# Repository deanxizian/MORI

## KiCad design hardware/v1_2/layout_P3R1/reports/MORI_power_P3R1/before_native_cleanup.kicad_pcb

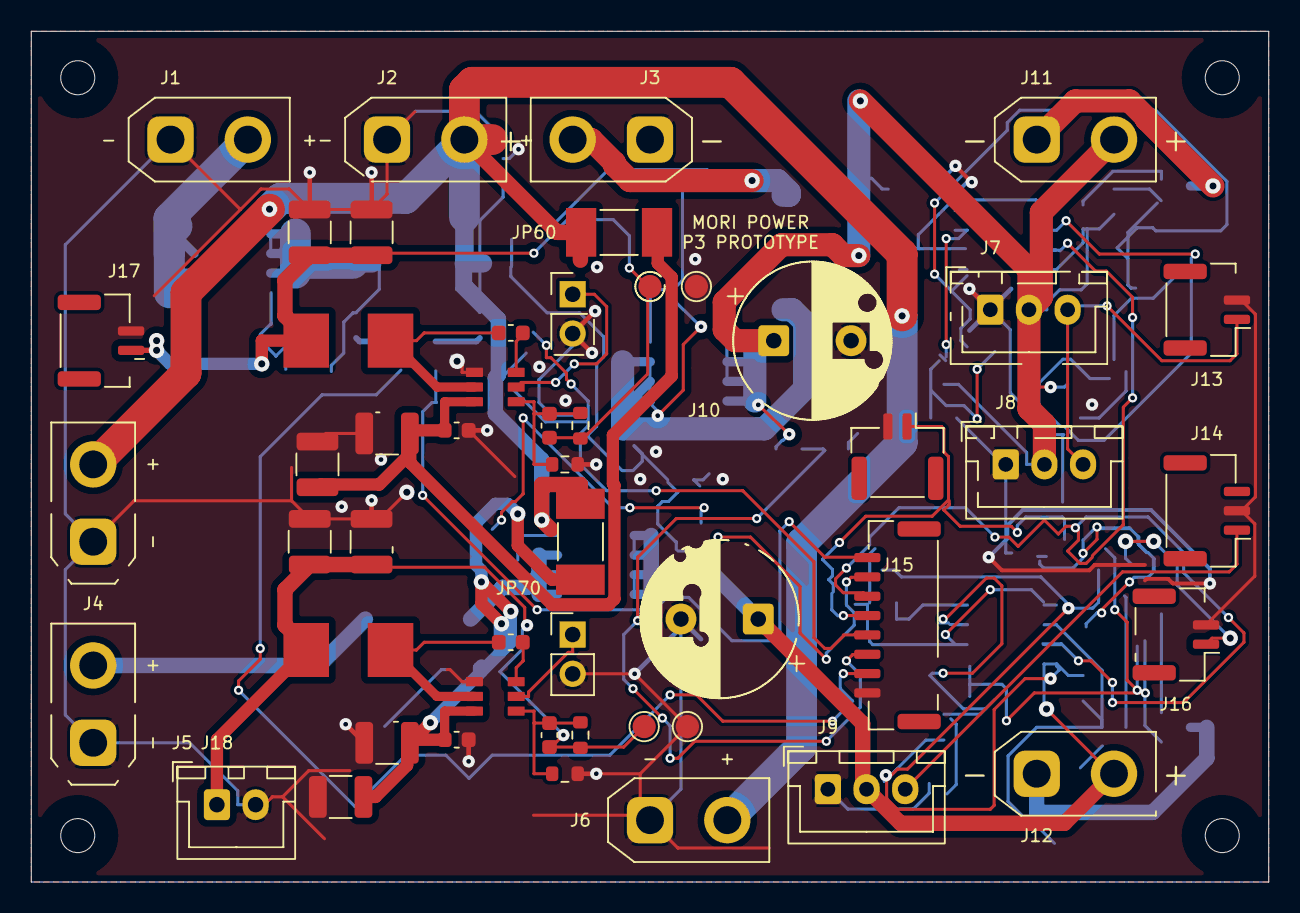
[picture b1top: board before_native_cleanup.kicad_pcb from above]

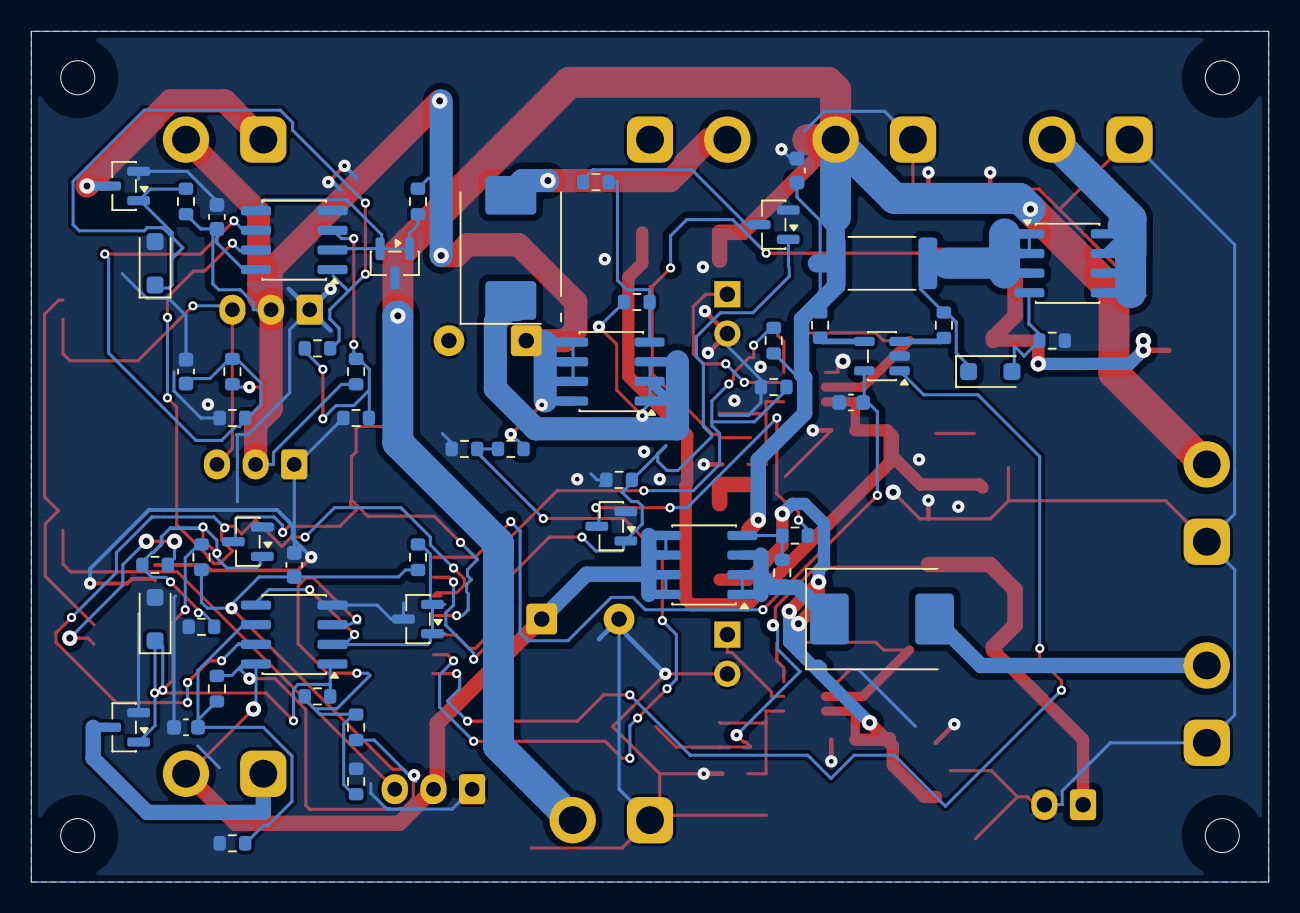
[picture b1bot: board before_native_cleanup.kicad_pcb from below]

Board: 2 copper layers, 80.0 x 55.0 mm, 107 parts (53 on the bottom side), 50 nets.

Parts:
C1, C20, C40: 100n; C_0603_1608Metric
C2: 1u 25V; C_0603_1608Metric__P3_C2
C10: Panasonic EEU-FR1C102 1000uF 16V; CP_Radial_D10.0mm_P5.00mm__P2_C10__P3_C10
C21, C41: 10n; C_0603_1608Metric
C30: Panasonic EEU-FR1C102 1000uF 16V; CP_Radial_D10.0mm_P5.00mm__P3_C30
C60: 22u / 25V / X7R; C_1210_3225Metric__P3_C60
C61, C62, C71, C72: 100n / 50V / X7R; C_0603_1608Metric
C63, C64, C66, C73, C76: 22u / 25V / X7R; C_1210_3225Metric
C65, C75: 75p / 50V / C0G; C_0603_1608Metric
C70: 22u / 25V / X7R; C_1210_3225Metric__P3_C70
C74: 22u / 25V / X7R; C_1210_3225Metric__P3_C74
D1, D20, D40: BZT52H-C10,115; D_SOD-123F
D10: B540C-13-F; D_SMC__P3_D10
D30: B540C-13-F; D_SMC
F60: 1A / 125V / very fast; Fuse_Littelfuse-NANO2-451_453
F70: 2A / 125V / very fast; Fuse_Littelfuse-NANO2-451_453
H1, H2, H3, H4: M2 mounting / POSITION TBD; MountingHole_2.2mm_M2
J1: PACK AFTER 6.3A FUSE / MASTER; AMASS_XT30UPB-M_1x02_P5.0mm_Vertical__P3_J1
J2: WHEEL BUCK VIN; AMASS_XT30UPB-M_1x02_P5.0mm_Vertical__P3_J2
J3: WHEEL BUCK 9V RETURN; AMASS_XT30UPB-M_1x02_P5.0mm_Vertical
J4: HEAD BUCK VIN; AMASS_XT30UPB-M_1x02_P5.0mm_Vertical__P2_J4__P3_J4
J5: HEAD BUCK 6V RETURN; AMASS_XT30UPB-M_1x02_P5.0mm_Vertical__P2_J5__P3_J5
J6: RAW BAT SERVICE / DNP; AMASS_XT30UPB-M_1x02_P5.0mm_Vertical__P3_J6
J7: S288 L; JST_XH_B3B-XH-A_1x03_P2.50mm_Vertical__P2_J7__P3_J7
J8: S288 R; JST_XH_B3B-XH-A_1x03_P2.50mm_Vertical__P2_J8
J9: SCS0009 CHAIN; JST_XH_B3B-XH-A_1x03_P2.50mm_Vertical
J10: MOTION CONTROL; JST_GH_BM08B-GHS-TBT_1x08-1MP_P1.25mm_Vertical__P2_J10__P3_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
J11: WHEEL DUMP 5R6 EXTERNAL; AMASS_XT30UPB-M_1x02_P5.0mm_Vertical
J12: HEAD DUMP 10R EXTERNAL; AMASS_XT30UPB-M_1x02_P5.0mm_Vertical__P2_J12
J13: S288 DATA; JST_GH_BM02B-GHS-TBT_1x02-1MP_P1.25mm_Vertical__P2_J13
J14: HEAD DATA; JST_GH_BM03B-GHS-TBT_1x03-1MP_P1.25mm_Vertical
J15: CHARGE INTERLOCK; JST_GH_BM02B-GHS-TBT_1x02-1MP_P1.25mm_Vertical
J16: CHARGER RAW VBUS SENSE; JST_GH_BM02B-GHS-TBT_1x02-1MP_P1.25mm_Vertical__P2_J16
J17: MOTION 5V OUT / 1+ 2GND; JST_GH_BM02B-GHS-TBT_1x02-1MP_P1.25mm_Vertical__P3_J17
J18: CAM 5V OUT / 1+ 2GND; JST_XH_B2B-XH-A_1x02_P2.50mm_Vertical
JP60: SERVICE OFF / OPEN=ON; PinHeader_1x02_P2.54mm_Vertical__P3_JP60
JP70: SERVICE OFF / OPEN=ON; PinHeader_1x02_P2.54mm_Vertical
L60, L70: 10uH / SRP7050TA-100M; Bourns_SRP7050TA_8p4_span_2p5_gap
Q1, Q10, Q30: AO4407A; SOIC-8_3.9x4.9mm_P1.27mm
Q11, Q20, Q31, Q40: AO3400A; SOT-23
Q50: MMBT3904LT1G; SOT-23
R1, R10, R30, R54: 10k; R_0603_1608Metric
R2: WSL2512R0100FEA 10mR 1% 1W; R_2512_6332Metric
R3, R4: 0; R_0603_1608Metric
R11, R31: 100; R_0603_1608Metric
R20, R24, R40, R44: 2.2k; R_0603_1608Metric
R21: 33.2k 0.1%; R_0603_1608Metric
R22, R26, R42, R46: 10k 0.1%; R_0603_1608Metric
R23, R43: 1M 0.1%; R_0603_1608Metric
R25: 37.4k 0.1%; R_0603_1608Metric
R41: 16.5k 0.1%; R_0603_1608Metric
R45: 18.7k 0.1%; R_0603_1608Metric
R50, R52: 100k 0.1%; R_0603_1608Metric
R51, R53: 27k 0.1%; R_0603_1608Metric
R55: 47k; R_0603_1608Metric
R56: 100k; R_0603_1608Metric
R60, R70: 100k / 0.1%; R_0603_1608Metric
R61: 13.3k / 0.1%; R_0603_1608Metric
R71: 13.3k / 0.1%; R_0603_1608Metric__P3_R71
TP60: +5V_MOTION; TestPoint_Pad_D1.5mm__P3_TP60
TP61, TP71: GND; TestPoint_Pad_D1.5mm
TP70: +5V_CAM; TestPoint_Pad_D1.5mm
U1: INA180A1IDBVR; SOT-23-5
U20, U40: LM393BDR; SOIC-8_3.9x4.9mm_P1.27mm
U21, U41: TL431BIDBZR; SOT-23
U60, U70: TPS54302DDCR; TI_DDC0006A_TPS54302

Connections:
/+3V3: C1.1, J10.1, U1.5
/+5V_CAM: C73.1, C74.1, C75.1, J18.1, L70.2, R70.1, TP70.1
/+5V_MOTION: C63.1, C64.1, C65.1, J17.1, L60.2, R60.1, TP60.1
/ARM_Q: J10.2, Q11.1, Q31.1, R54.1
/BAT_ADC: J10.5, R50.2, R51.1
/BAT_IN: J1.2, Q1.5, Q1.6, Q1.7, Q1.8
/BAT_MON: C2.1, F60.1, F70.1, J2.2, J4.2, J6.2, R2.2, R4.1, R50.1
/BAT_REV: D1.1, Q1.1, Q1.2, Q1.3, R2.1, R3.1
/C5_BOOT: C72.1, U70.6
/C5_EN: JP70.1, U70.5
/C5_FB: C75.2, R70.2, R71.1, U70.4
/C5_SW: C72.2, L70.1, U70.2
/C5_VIN: C70.1, C71.1, C76.1, F70.2, U70.3
/CHG_BASE: Q50.1, R55.2, R56.1
/CHG_N: J10.4, J15.1, Q50.3
/CURRENT_ADC: J10.7, U1.1
/FAULT_N: J10.3, U20.7, U40.7
/GND: C1.2, C2.2, C10.2, C20.2, C21.2, C30.2, C40.2, C41.2, C60.2, C61.2, C63.2, C64.2, C66.2, C70.2, C71.2, C73.2, C74.2, C76.2, D20.2, D40.2, J1.1, J2.1, J3.1, J4.1, J5.1, J6.1, J7.1, J8.1, J9.1, J10.8, J13.2, J14.2, J15.2, J16.2, J17.2, J18.2, JP60.2, JP70.2, Q11.2, Q20.2, Q31.2, Q40.2, Q50.2, R1.2, R22.2, R26.2, R42.2, R46.2, R51.2, R53.2, R54.2, R56.2, R61.2, R71.2, TP61.1, TP71.1, U1.2, U20.4, U21.3, U40.4, U41.3, U60.1, U70.1
/H6_IN: D30.2, J5.2
/H_BRAKE_GATE: D40.1, Q40.1, R43.1, R44.2, U40.1
/H_BUS: J9.3, J14.1
/H_DUMP_D: J12.1, Q40.3
/H_GATE: Q30.4, R30.1, R31.1
/H_GATE_LOW: Q31.3, R31.2
/H_OVSENSE: C41.1, R45.2, R46.1, U40.6
/H_PRE: D30.1, Q30.1, Q30.2, Q30.3, R30.2
/H_REF: R40.2, U40.2, U40.5, U41.1, U41.2
/H_SENSE: R41.2, R42.1, R43.2, U40.3
/H_VM: C30.1, C40.1, J9.2, J12.2, Q30.5, Q30.6, Q30.7, Q30.8, R40.1, R41.1, R44.1, R45.1, U40.8
/KELVIN_N: R4.2, U1.4
/KELVIN_P: R3.2, U1.3
/M5_BOOT: C62.1, U60.6
/M5_EN: JP60.1, U60.5
/M5_FB: C65.2, R60.2, R61.1, U60.4
/M5_SW: C62.2, L60.1, U60.2
/M5_VIN: C60.1, C61.1, C66.1, F60.2, U60.3
/REV_GATE: D1.2, Q1.4, R1.1
/VBUS_CHARGE: J16.1, R55.1
/W9_IN: D10.2, J3.2
/WHEEL_ADC: J10.6, R52.2, R53.1
/W_BRAKE_GATE: D20.1, Q20.1, R23.1, R24.2, U20.1
/W_BUS: J7.3, J8.3, J13.1
/W_DUMP_D: J11.1, Q20.3
/W_GATE: Q10.4, R10.1, R11.1
/W_GATE_LOW: Q11.3, R11.2
/W_OVSENSE: C21.1, R25.2, R26.1, U20.6
/W_PRE: D10.1, Q10.1, Q10.2, Q10.3, R10.2
/W_REF: R20.2, U20.2, U20.5, U21.1, U21.2
/W_SENSE: R21.2, R22.1, R23.2, U20.3
/W_VM: C10.1, C20.1, J7.2, J8.2, J11.2, Q10.5, Q10.6, Q10.7, Q10.8, R20.1, R21.1, R24.1, R25.1, R52.1, U20.8

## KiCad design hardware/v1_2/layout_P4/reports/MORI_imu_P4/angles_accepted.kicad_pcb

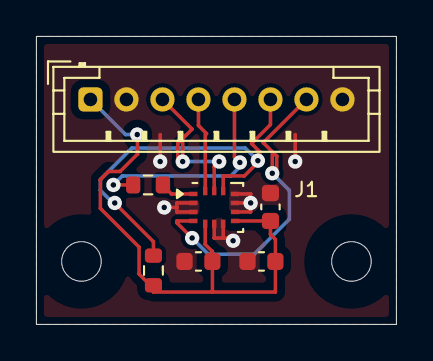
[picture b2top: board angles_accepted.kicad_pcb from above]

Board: 2 copper layers, 20.0 x 16.0 mm, 9 parts (0 on the bottom side), 8 nets.

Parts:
C1: 100n; C_0603_1608Metric
C2: 2.2u; C_0603_1608Metric
C3: 10n; C_0603_1608Metric
H1, H2: M2 clearance; MountingHole_2.2mm_M2
J1: BODY RIGID IMU; JST_PH_B8B-PH-K_1x08_P2.00mm_Vertical__P4_PH_ANNULUS
R1: 33; R_0603_1608Metric
R2: 10k; R_0603_1608Metric
U1: ICM-42688-P; TDK_ICM42688P_LGA14_3x2p5__P2_U1__P3R1_U1

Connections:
/+3V3: C1.1, C2.1, C3.1, J1.1, R2.2, U1.5, U1.8
/CS_N: J1.6, R2.1, U1.12
/DRDY: J1.7, U1.4
/GND: C1.2, C2.2, C3.2, J1.2, J1.8, U1.2, U1.3, U1.6, U1.7, U1.9, U1.10, U1.11
/MISO: J1.5, R1.2
/MISO_IC: R1.1, U1.1
/MOSI: J1.4, U1.14
/SCK: J1.3, U1.13
